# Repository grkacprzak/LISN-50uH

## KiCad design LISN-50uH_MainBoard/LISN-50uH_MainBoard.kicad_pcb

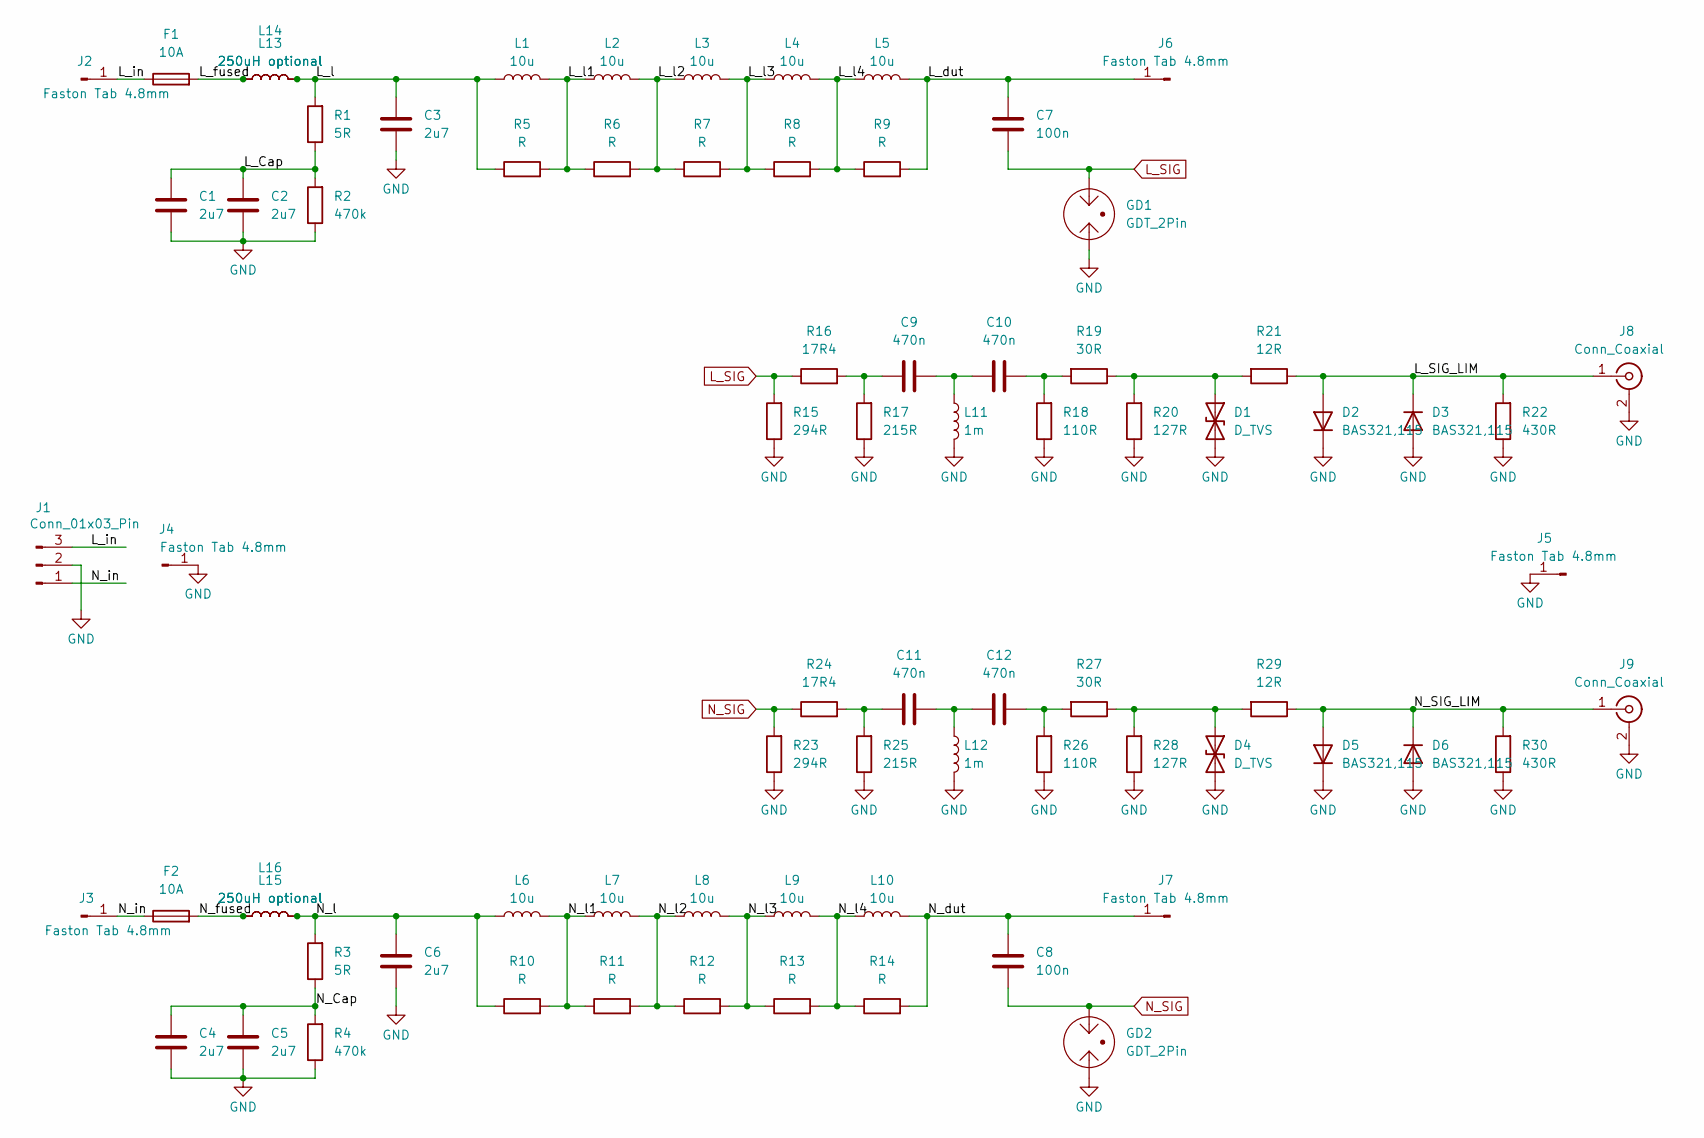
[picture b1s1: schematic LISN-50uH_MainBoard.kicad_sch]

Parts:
C1, C2, C3, C4, C5, C6: 2u7; C_Rect_L28.0mm_W12.0mm_P22.50mm_MKS4
C7, C8: 100n; C_Rect_L19.0mm_W11.0mm_P15.00mm_MKS4
C9, C10, C11, C12: 470n; C_0805_2012Metric
D1, D4: D_TVS; D_SOD-323
D2, D3, D5, D6: BAS321,115; D_SOD-323
F1, F2: 10A; Fuseholder_Clip-5x20mm_Littelfuse_100_111_dual_Horizontal; MPN 01110501Z or 01000056Z
GD1, GD2: GDT_2Pin; GDT_D8_P10.16_Horizontal
J1: Conn_01x03_Pin; AC_Connector_Adam_tech_IEC-A-4
J2, J3, J4, J5, J6, J7: Faston Tab 4.8mm; Faston_Tab_4.8x0.8
J8, J9: Conn_Coaxial; U.FL_Molex_MCRF_73412-0110_Vertical
L1, L2, L3, L4, L5, L6, L7, L8, L9, L10: 10u; L_Wuerth_HCC-1210
L11, L12: 1m; L_1812_4532Metric_Pad1.30x3.40mm_HandSolder
L13, L16: 250uH optional; L_Toroid_Horizontal_D42.0mm_H21.5mm_Abracon_ATCA-08
L14, L15: 250uH optional; L_Toroid_Vertical_L38.0mm_W16.0mm_P15.0mm_Wuerth_WE-FI
R1, R3: 5R; R_Axial_DIN0414_L11.9mm_D4.5mm_P15.24mm_Horizontal
R2, R4: 470k; R_2010_5025Metric
R5, R6, R7, R8, R9, R10, R11, R12, R13, R14: R; R_2010_5025Metric
R15, R23: 294R; R_0805_2012Metric
R16, R24: 17R4; R_0805_2012Metric
R17, R25: 215R; R_0805_2012Metric
R18, R26: 110R; R_0805_2012Metric
R19, R27: 30R; R_0805_2012Metric
R20, R28: 127R; R_0805_2012Metric
R21, R29: 12R; R_0805_2012Metric
R22, R30: 430R; R_0805_2012Metric

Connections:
/L_Cap: C1.1, C2.1, R1.1, R2.2
/L_SIG_LIM: D2.2 (A), D3.1 (K), J8.1 (In), R21.1, R22.2
/L_dut: C7.1, J6.1, L5.2, R9.2
/L_fused: F1.2, L13.1, L14.1
/L_in: F1.1, J1.3, J2.1
/L_l: C3.1, L1.1, L13.2, L14.2, R1.2, R5.1
/L_l1: L1.2, L2.1, R5.2, R6.1
/L_l2: L2.2, L3.1, R6.2, R7.1
/L_l3: L3.2, L4.1, R7.2, R8.1
/L_l4: L4.2, L5.1, R8.2, R9.1
/N_Cap: C4.1, C5.1, R3.1, R4.2
/N_SIG_LIM: D5.2 (A), D6.1 (K), J9.1 (In), R29.1, R30.2
/N_dut: C8.1, J7.1, L10.2, R14.2
/N_fused: F2.2, L15.1, L16.1
/N_in: F2.1, J1.1, J3.1
/N_l: C6.1, L6.1, L15.2, L16.2, R3.2, R10.1
/N_l1: L6.2, L7.1, R10.2, R11.1
/N_l2: L7.2, L8.1, R11.2, R12.1
/N_l3: L8.2, L9.1, R12.2, R13.1
/N_l4: L9.2, L10.1, R13.2, R14.1
GND: C1.2, C2.2, C3.2, C4.2, C5.2, C6.2, D1.2 (A2), D2.1 (K), D3.2 (A), D4.2 (A2), D5.1 (K), D6.2 (A), GD1.1, GD2.1, J1.2, J4.1, J5.1, J8.2 (Ext), J9.2 (Ext), L11.2, L12.2, R2.1, R4.1, R15.1, R17.1, R18.1, R20.1, R22.1, R23.1, R25.1, R26.1, R28.1, R30.1
L_SIG: C7.2, GD1.3, R15.2, R16.1
N_SIG: C8.2, GD2.3, R23.2, R24.1
unnamed: C9.1, R16.2, R17.2
unnamed: C9.2, C10.1, L11.1
unnamed: C10.2, R18.2, R19.2
unnamed: C11.1, R24.2, R25.2
unnamed: C11.2, C12.1, L12.1
unnamed: C12.2, R26.2, R27.2
unnamed: D1.1 (A1), R19.1, R20.2, R21.2
unnamed: D4.1 (A1), R27.1, R28.2, R29.2

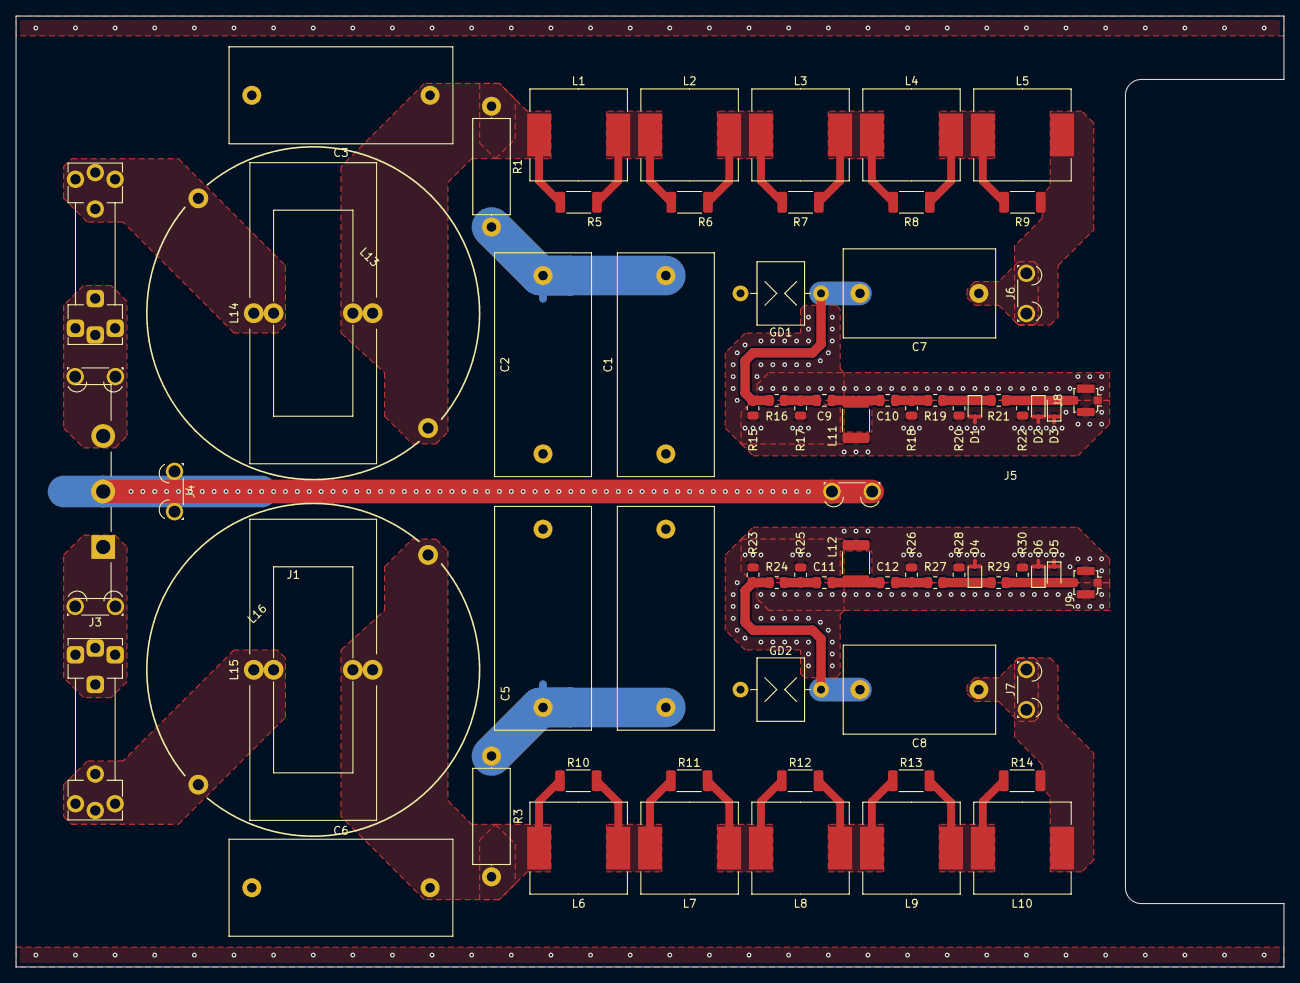
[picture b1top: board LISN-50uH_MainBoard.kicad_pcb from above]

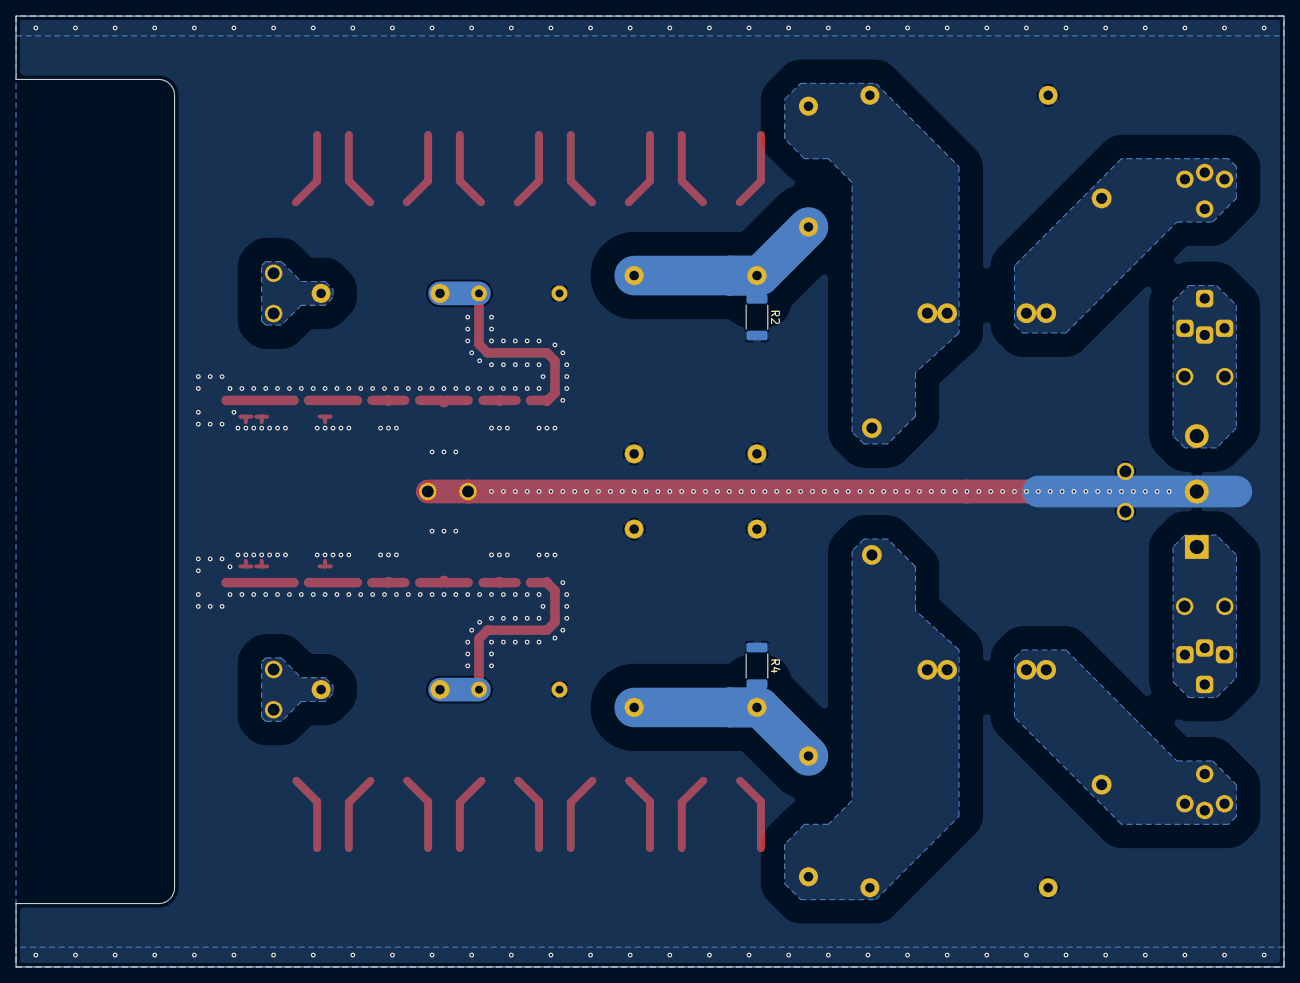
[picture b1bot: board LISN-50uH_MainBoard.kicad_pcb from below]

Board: 2 copper layers, 160.0 x 120.0 mm, 77 parts (2 on the bottom side), 31 nets.

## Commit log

2025-01-27 initial - test board
2025-01-28 sch update - changes in filter path. pcb - change PCB dimensions
2025-01-28 changes in low pass filter/limiter path
2025-01-29 sch - add GDT and optional input toroidal line choke pcb - routing in progress
2025-01-31 change input coil footprint, add RF transformer for CM/DM
2025-02-06 add L&N/CM&DM switch
2025-02-07 Planes added
2025-02-10 add RF track via shielding
2025-02-10 move SWitch outline and silk to center
2025-04-30 move CM DM to dedicated PCB
